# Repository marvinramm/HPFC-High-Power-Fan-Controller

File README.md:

# HPFC – High Power Fan Controller

**Controller for four 12 V server fans with up to 100 W, built into a DIY air filter. It measures the pressure drop across the filter with two BME680 sensors, has its own OLED display and rotary encoder, and joins Zigbee networks, e.g. Home Assistant through Zigbee2MQTT.**

I built the HPFC in 2025 for my own air filter: four Arctic server fans at 8000 RPM move the air through a filter in a closed box. A server fan is loud and needs a lot of power, so it needs a controller that runs it as slowly as possible and tells me when the filter is clogged. The HPFC does that: it compares the air pressure before and after the filter, shows the filter load on the display and on the RGB LED, and reports it to Home Assistant.

## Features

- **4 fan channels** for standard 4-pin PWM fans: 25 kHz PWM, tach input on every channel, 12 V rail switched off completely when the fans stop
- **Up to about 100 W** fan power on one 12 V rail (tested with four Arctic server fans, 8000 RPM)
- **Power supply:**
  - external **12 V** supply on a screw terminal, full fan power
  - or **USB-C Power Delivery**: the CH224K requests 12 V from a PD charger, fan power limited by the firmware
  - LM74700 ideal diode on the USB-C input, so both sources can be connected at the same time without back-feeding the USB port
  - on plain 5 V USB the board runs (display, Zigbee, flashing), the fans stay off
- **Filter monitoring:** two BME680 sensors, one on each side of the filter. The pressure difference is shown as filter load in percent; the LED turns green, yellow or red.
- **Climate data:** temperature and humidity of the air
- **Zigbee 3.0 router** with the ESP32-C6: fan speed 0–100 %, temperature, humidity and filter load as Zigbee endpoints, external converter for [Zigbee2MQTT](firmware/zigbee2mqtt/HPFC.js)
- **Local UI:** 0.96" OLED, rotary encoder with push button, display turns off after 200 s without input
- **ESP32-C6-MINI-1** with native USB on the USB-C port, Tag-Connect TC2050 for programming

## How it works

```mermaid
flowchart LR
    PSU["12 V supply"] --> RAIL["12 V rail"]
    USB["USB-C"] --> PD["CH224K<br/>PD 12 V"]
    USB --> ID["Ideal diode<br/>LM74700 + AO4406"] --> RAIL
    RAIL --> SWITCH["Fan rail switch<br/>AOD403"] --> FANS["4 × server fan"]
    RAIL --> LDO["AMS1117<br/>3.3 V"] --> ESP["ESP32-C6"]
    ESP -- "4 × PWM 25 kHz" --> FANS
    FANS -- "4 × tach" --> ESP
    ESP -- FAN_EN --> SWITCH
    BME1["BME680<br/>before filter"] <-- I²C --> ESP
    BME2["BME680<br/>after filter"] <-- I²C --> ESP
    ESP <-- I²C --> OLED["OLED display"]
    ENC["Rotary encoder"] --> ESP
    ESP --> LED["RGB LED"]
    ESP <-. Zigbee .-> HA["Zigbee2MQTT /<br/>Home Assistant"]
```

## The air filter

The HPFC sits behind the front panel of the filter box. The four fans are mounted under the filter layer and move the air through it. The second BME680 is connected to the I²C header with a short cable and sits on the other side of the filter, so the controller can measure the pressure difference across it.

## Display and status LED

| Page | Content |
|---|---|
| Fan speed | Fan speed in %, power source (`USB 5V`, `USB PD 12V`, `Internal Supply`), Zigbee status |
| Filter pressure | Filter load in % (pressure difference relative to `MAXPADELTA`, default 350 Pa) |

Press the encoder to switch pages. The RGB LED shows the filter load: green below 45 %, yellow from 45 %, red from 70 % – time to change the filter.

## Firmware

HPFOS V0.1.4, Arduino with ESP32 core 3.3. Build instructions, settings, the Zigbee endpoints and the Zigbee2MQTT setup are in [`firmware/README.md`](firmware/README.md).

## Hardware

| | |
|---|---|
| PCB | 2 layers, 71.5 × 50.85 mm, 1.6 mm |
| Schematic | [`hardware/hpfc-v1/HPFC-V1_schematic.pdf`](hardware/hpfc-v1/HPFC-V1_schematic.pdf) |
| BOM | [`hardware/hpfc-v1/HPFC-V1_BOM.csv`](hardware/hpfc-v1/HPFC-V1_BOM.csv), [interactive BOM](hardware/hpfc-v1/HPFC-V1_ibom.html) |
| Design files | EAGLE / Fusion Electronics in [`hardware/hpfc-v1/source`](hardware/hpfc-v1/source) |
| Fabrication data | ODB++ and Gerber in the [release](https://github.com/marvinramm/HPFC-High-Power-Fan-Controller/releases) |

Block description and pin assignment: [`hardware/README.md`](hardware/README.md).

## License

© 2025 Marvin Ramm. Free for **non-commercial** use with attribution:

- Firmware (`firmware/`): [PolyForm Noncommercial 1.0.0](LICENSE)
- Hardware and documentation: [CC BY-NC 4.0](hardware/LICENSE)

Credit "HPFC by Marvin Ramm" with a link to this repository. **Selling boards, kits or products based on the HPFC needs my agreement**, e.g. with a share of the profit – contact marvin@ramm-eng.de. Details are in [LICENSING.md](LICENSING.md).

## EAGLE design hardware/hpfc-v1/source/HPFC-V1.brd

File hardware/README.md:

# Hardware

| File | Content |
|---|---|
| [`hpfc-v1/HPFC-V1_schematic.pdf`](hpfc-v1/HPFC-V1_schematic.pdf) | Schematic (1 sheet, A3) |
| [`hpfc-v1/HPFC-V1_BOM.csv`](hpfc-v1/HPFC-V1_BOM.csv) | Bill of materials, 74 parts |
| [`hpfc-v1/HPFC-V1_ibom.html`](hpfc-v1/HPFC-V1_ibom.html) | Interactive BOM for assembly (download and open in a browser) |
| [`hpfc-v1/source`](hpfc-v1/source) | Schematic and board as EAGLE files (Fusion Electronics 9.7) |

The fabrication data is attached to the [release](https://github.com/marvinramm/HPFC-High-Power-Fan-Controller/releases):

- **ODB++** exported from Fusion Electronics – the original data, accepted directly by most PCB manufacturers
- **Gerber + Excellon drill** generated from the EAGLE board with KiCad's EAGLE importer, including the slotted holes of the USB-C connector. Check them in a Gerber viewer before you order.

## Board

2 layers, 71.5 × 50.85 mm, 1.6 mm, four M3 mounting holes. The display, the encoder, the USB-C port and almost all parts are on the top side. The fan connectors, the 12 V terminal, the bulk capacitor C7 and the I²C header for the second sensor are on the bottom, so the board can sit directly behind a front panel.

| Block | Parts | Function |
|---|---|---|
| USB-C | J7, D1 (SP0503BAHTG) | Power input and native USB, ESD protection |
| USB-PD trigger | IC1 (CH224K) | Requests 12 V from a USB-PD charger |
| Ideal diode | IC3 (LM74700-Q1), Q1 (AO4406AL) | Connects USB-C VBUS to the 12 V rail and blocks reverse current, so an external 12 V supply never feeds back into the USB port |
| External supply | J1 (Phoenix 1711026) | 12 V screw terminal, directly on the 12 V rail |
| Fan rail switch | Q2 (AOD403, P-MOSFET), Q3 (SI2302) | Switches 12 V to all four fans (`FAN_EN`, GPIO22) |
| Fan connectors | J2–J5 (Molex 47053) | Standard 4-pin PWM fan headers: 12 V, GND, PWM (25 kHz), tach |
| Tach filter | R7–R18, C8–C11 | 10 kΩ pull-up to 3.3 V and 2.2 kΩ / 180 pF low-pass for each tach signal |
| 3.3 V | IC4 (AMS1117-3.3) | LDO from the 12 V rail, 1 A |
| MCU | IC5 (ESP32-C6-MINI-1-N4) | Zigbee / Thread, Wi-Fi 6, BLE, 4 MB flash |
| Sensors | IC2 (BME680), JP2 | BME680 on the board, second BME680 on the I²C header JP2 |
| User interface | DSP1 (SSD1306 0.96" OLED), SW1 (PEC12R encoder), LED1 (RGB) | Display, rotary encoder with push button, status LED |
| Programming | J6 (TC2050), SW2 (BOOT), SW3 (RESET) | Tag-Connect with USB D+/D−, EN and BOOT |
| Voltage sense | R2/R5, R3/R6 | Dividers for USB-C VBUS (GPIO1) and the 12 V rail (GPIO2) |

## ESP32-C6 pin assignment

| GPIO | Function | | GPIO | Function |
|---|---|---|---|---|
| 0 | LED blue | | 14–17 | PWM fan 1–4 |
| 1 | USB-C voltage (ADC) | | 18–21 | Tach fan 1–4 |
| 2 | 12 V rail voltage (ADC) | | 22 | `FAN_EN` (12 V fan rail) |
| 3 | LED red | | 23 | LED green |
| 4 | Encoder button | | 12 / 13 | USB D− / D+ |
| 5 / 8 | Encoder A / B | | 9 | BOOT button |
| 6 / 7 | I²C SDA / SCL | | | |

I²C addresses: BME680 on the board `0x77` (address set with JP1), BME680 on JP2 `0x76`, OLED `0x3C`.

## Power budget

The four fans share one 12 V rail. With four Arctic server fans at 8000 RPM the HPFC switches up to about 100 W. Use an external 12 V supply for full speed. On USB-PD the firmware limits the PWM to about 35 %, and on plain 5 V USB the fans stay off (see [firmware](../firmware/README.md#power-source-and-fan-limit)).

## License

The hardware design files and documentation are licensed under [CC BY-NC 4.0](LICENSE). Commercial use needs my agreement, see [LICENSING.md](../LICENSING.md).

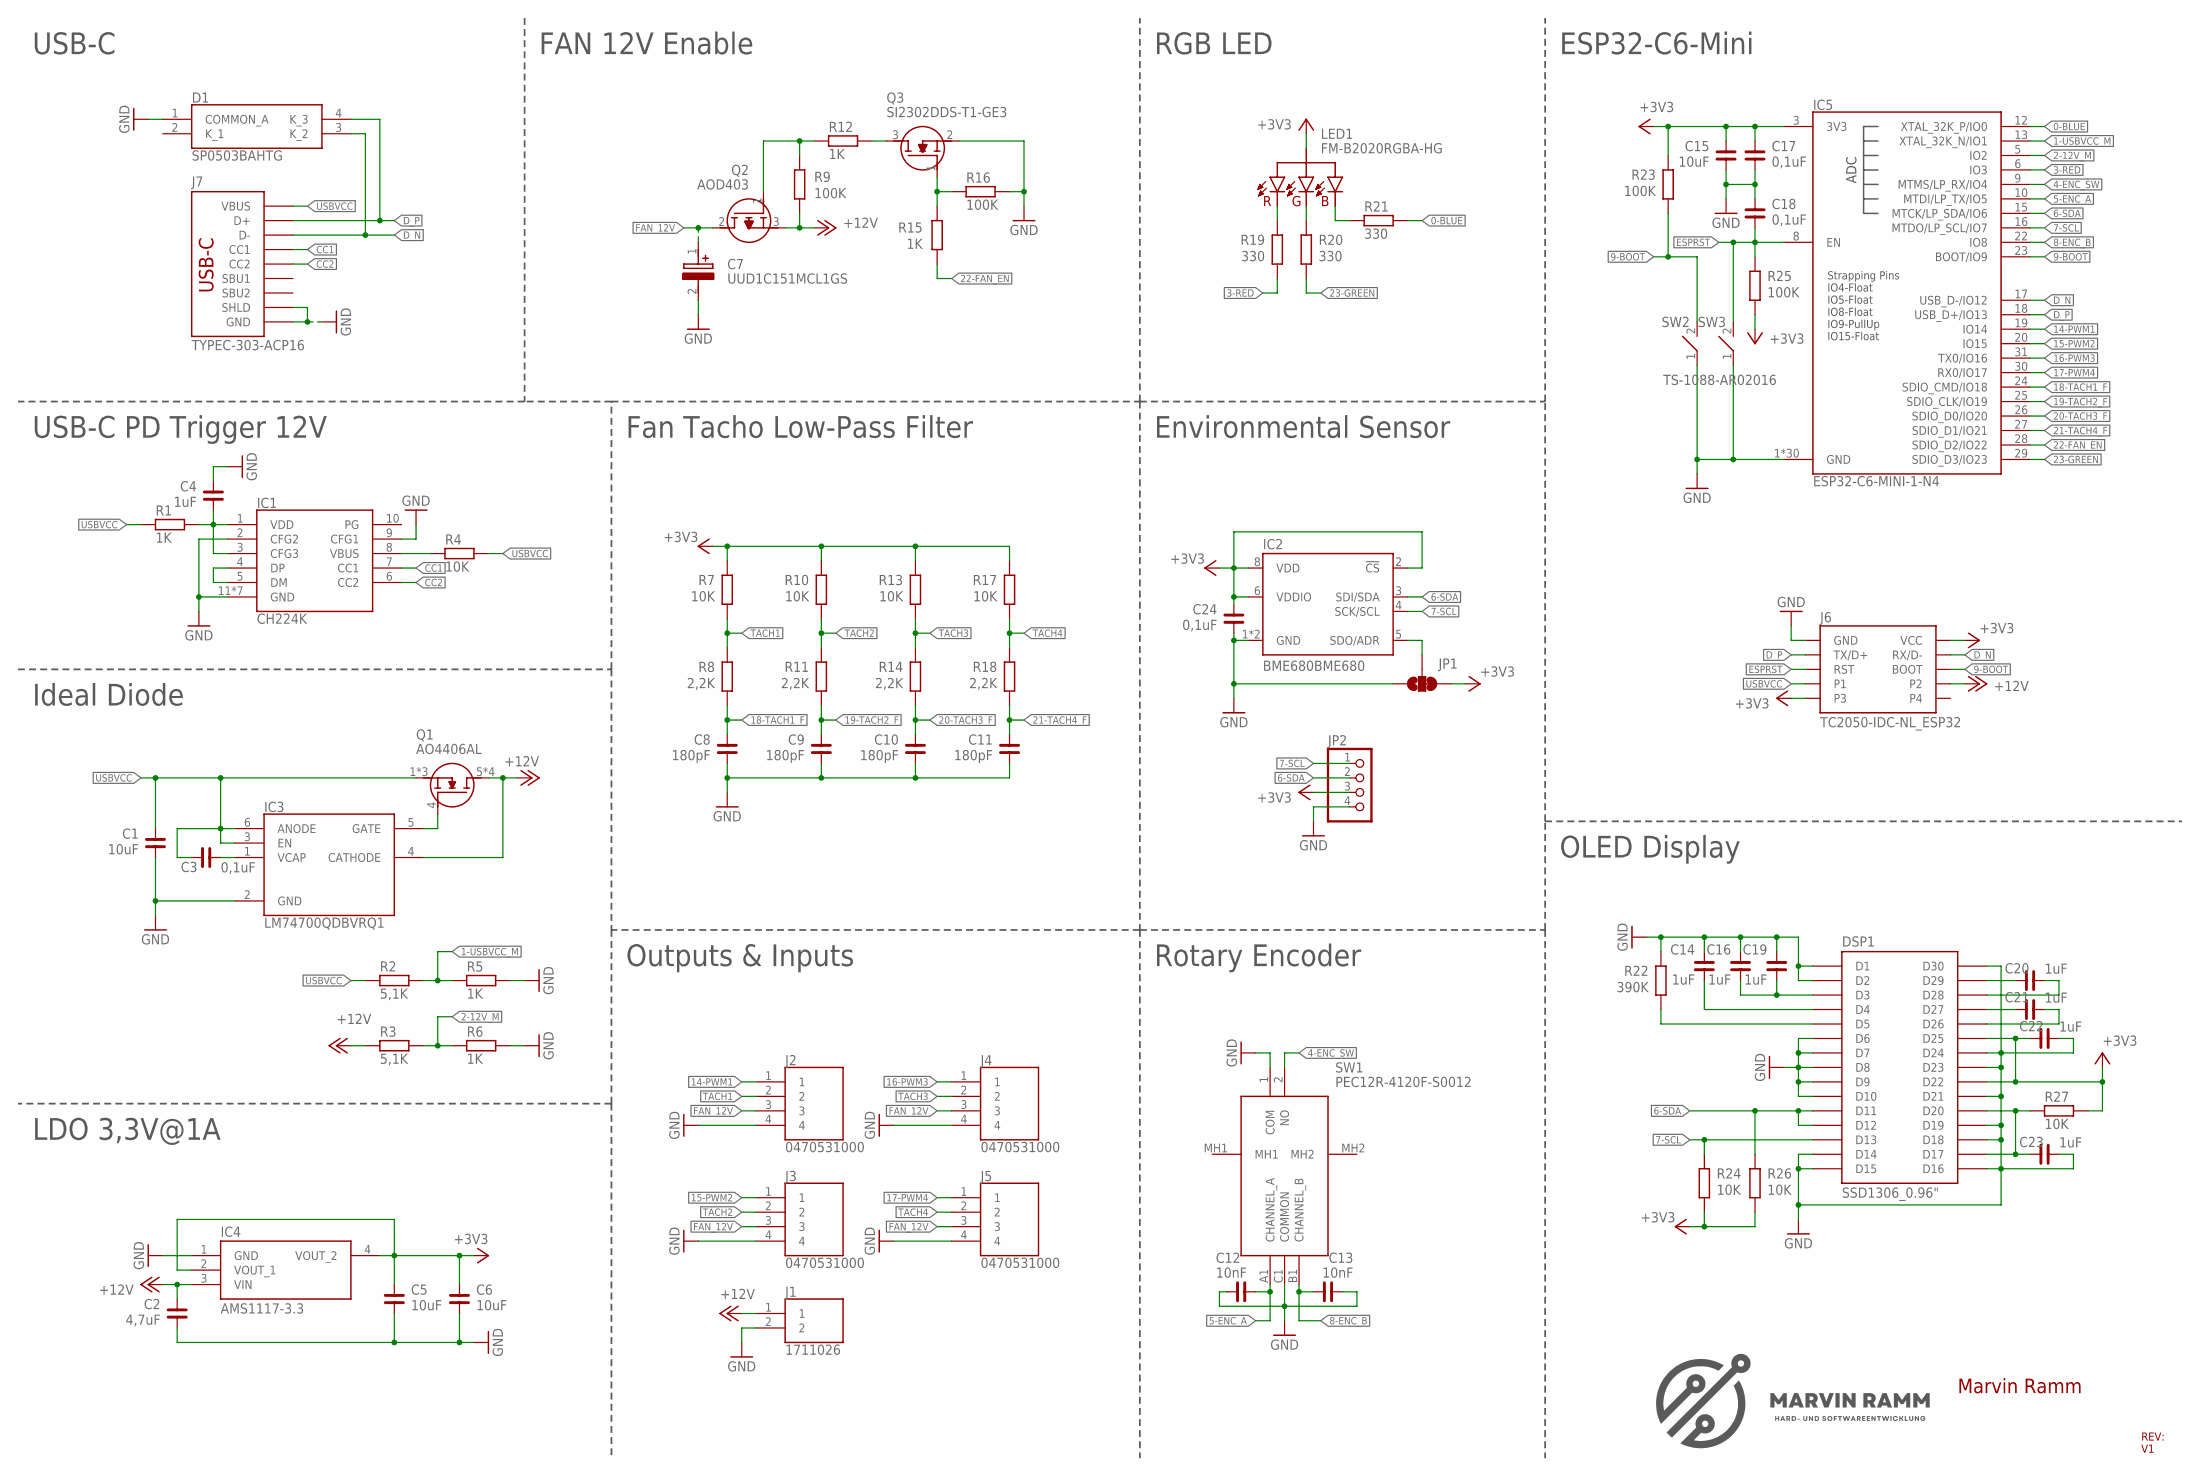
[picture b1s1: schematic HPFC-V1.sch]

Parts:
C1, C5, C6, C15: 10uF; C0603
C2: 4,7uF; C0603
C3, C17, C18, C24: 0,1uF; C0402
C4, C14, C16, C19, C20, C21, C22, C23: 1uF; C0402
C7: UUD1C151MCL1GS; CAPAE660X800N
C8, C9, C10, C11: 180pF; C0402
C12, C13: 10nF; C0402
D1: SP0503BAHTG
DSP1: SSD1306_0.96"
IC1: CH224K; SOP100P600X180-11N
IC2: BME680BME680; LGA3.0X3.0
IC3: LM74700QDBVRQ1; SOT95P280X145-6N
IC4: AMS1117-3.3; SOT229P700X180-4N
IC5: ESP32-C6-MINI-1-N4; ESP32C6MINI1N4
J1: 1711026
J2, J3, J4, J5: 0470531000
J6: TC2050-IDC-NL_ESP32; TC2050-IDC-NL
J7: TYPEC-303-ACP16
JP1: JUMPER-SMT_3_1-NC_TRACE_SILK; SMT-JUMPER_3_1-NC_TRACE_SILK
JP2: PINHD-1X4; 1X04
LED1: FM-B2020RGBA-HG; FMB2020RGBAHG
Q1: AO4406AL; SOIC127P600X175-8N
Q2: AOD403; AOD480
Q3: SI2302DDS-T1-GE3; SOT95P237X112-3N
R1, R5, R6, R12, R15: 1K; R0402
R2, R3: 5,1K; R0402
R4, R7, R10, R13, R17, R24, R26, R27: 10K; R0402
R8, R11, R14, R18: 2,2K; R0402
R9, R16, R23, R25: 100K; R0402
R19, R20, R21: 330; R0402
R22: 390K; R0402
SW1: PEC12R-4120F-S0012; PEC12R4230FS0024
SW2, SW3: TS-1088-AR02016; TS1088AR02016

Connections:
0-BLUE: IC5.12 (XTAL_32K_P/IO0), R21.2
1-USBVCC_M: IC5.13 (XTAL_32K_N/IO1), R2.2, R5.1
2-12V_M: IC5.5 (IO2), R3.2, R6.1
3-RED: IC5.6 (IO3), R19.2
4-ENC_SW: IC5.9 (MTMS/LP_RX/IO4), SW1.2 (NO)
5-ENC_A: C12.2, IC5.10 (MTDI/LP_TX/IO5), SW1.A1 (CHANNEL_A)
6-SDA: DSP1.D11, DSP1.D12, IC2.3 (SDI/SDA), IC5.15 (MTCK/LP_SDA/IO6), JP2.2, R26.1
7-SCL: DSP1.D13, IC2.4 (SCK/SCL), IC5.16 (MTDO/LP_SCL/IO7), JP2.1, R24.1
8-ENC_B: C13.2, IC5.22 (IO8), SW1.B1 (CHANNEL_B)
9-BOOT: IC5.23 (BOOT/IO9), J6.6 (BOOT), R23.2, SW2.2 (NO)
14-PWM1: IC5.19 (IO14), J2.1
15-PWM2: IC5.20 (IO15), J3.1
16-PWM3: IC5.31 (TX0/IO16), J4.1
17-PWM4: IC5.30 (RX0/IO17), J5.1
18-TACH1_F: C8.2, IC5.24 (SDIO_CMD/IO18), R8.2
19-TACH2_F: C9.2, IC5.25 (SDIO_CLK/IO19), R11.2
20-TACH3_F: C10.2, IC5.26 (SDIO_D0/IO20), R14.2
21-TACH4_F: C11.2, IC5.27 (SDIO_D1/IO21), R18.2
22-FAN_EN: IC5.28 (SDIO_D2/IO22), R15.1
23-GREEN: IC5.29 (SDIO_D3/IO23), R20.2
+3V3: C5.2, C6.2, C15.2, C17.2, C22.1, C24.2, DSP1.D22, DSP1.D25, IC2.2 (!CS), IC2.6 (VDDIO), IC2.8 (VDD), IC4.2 (VOUT_1), IC4.4 (VOUT_2), IC5.3 (3V3), J6.2 (VCC), J6.9 (P3), JP1.3, JP2.3, LED1.3 (VCC), R7.1, R10.1, R13.1, R17.1, R23.1, R24.2, R25.2, R26.2, R27.2
+12V: C2.2, IC3.4 (CATHODE), IC4.3 (VIN), J1.1, J6.8 (P2), Q1.5 (D), Q1.6 (D), Q1.7 (D), Q1.8 (D), Q2.3 (S), R3.1, R9.1
CC1: IC1.7 (CC1), J7.A5 (CC1)
CC2: IC1.6 (CC2), J7.B5 (CC2)
D_N: D1.3 (K_2), IC5.17 (USB_D-/IO12), J6.4 (RX/D-), J7.A7 (D-), J7.B7 (D-)
D_P: D1.4 (K_3), IC5.18 (USB_D+/IO13), J6.3 (TX/D+), J7.A6 (D+), J7.B6 (D+)
ESPRST: C18.1, IC5.8 (EN), J6.5 (RST), R25.1, SW3.2 (NO)
FAN_12V: C7.1 (+), J2.3, J3.3, J4.3, J5.3, Q2.2 (D)
GND: C1.1, C2.1, C4.2, C5.1, C6.1, C7.2 (-), C8.1, C9.1, C10.1, C11.1, C12.1, C13.1, C14.2, C15.1, C16.2, C17.1, C18.2, C19.2, C22.2, C23.2, C24.1, D1.1 (COMMON_A), DSP1.D1, DSP1.D2, DSP1.D6, DSP1.D7, DSP1.D8, DSP1.D9, DSP1.D10, DSP1.D14, DSP1.D15, DSP1.D16, DSP1.D18, DSP1.D19, DSP1.D21, DSP1.D23, DSP1.D24, DSP1.D30, IC1.2 (CFG2), IC1.9 (CFG1), IC1.11 (GND), IC1.P$1 (GND), IC1.P$2 (GND), IC1.P$3 (GND), IC1.P$4 (GND), IC1.P$5 (GND), IC1.P$6 (GND), IC2.1 (GND), IC2.7 (GND), IC3.2 (GND), IC4.1 (GND), IC5.1 (GND), IC5.2 (GND), IC5.11 (GND), IC5.14 (GND), IC5.36 (GND), IC5.37 (GND), IC5.38 (GND), IC5.39 (GND), IC5.40 (GND), IC5.41 (GND), IC5.42 (GND), IC5.43 (GND), IC5.44 (GND), IC5.45 (GND), IC5.46 (GND), IC5.47 (GND), IC5.48 (GND), IC5.49 (GND), IC5.50 (GND), IC5.51 (GND), IC5.52 (GND), IC5.53 (GND), IC5.54 (GND), IC5.55 (GND), IC5.56 (GND), IC5.57 (GND), IC5.58 (GND), IC5.59 (GND), IC5.60 (GND), IC5.61 (GND), J1.2, J2.4, J3.4, J4.4, J5.4, J6.1 (GND), J7.A1 (GND), J7.A12 (GND), J7.B1 (GND), J7.B12 (GND), J7.PD1 (SHLD), J7.PD2 (SHLD), J7.PD3 (SHLD), J7.PD4 (SHLD), JP1.1, JP2.4, Q3.2 (S), R5.2, R6.2, R16.2, R22.1, SW1.1 (COM), SW1.C1 (COMMON), SW2.1 (COM), SW3.1 (COM)
unnamed: C4.1, IC1.1 (VDD), IC1.3 (CFG3), R1.2
unnamed: IC1.4 (DP), IC1.5 (DM)
unnamed: IC1.8 (VBUS), R4.1
unnamed: IC3.5 (GATE), Q1.4 (G1)
unnamed: LED1.2 (B), R21.1
unnamed: IC2.5 (SDO/ADR), JP1.2
unnamed: C3.2, IC3.1 (VCAP)
unnamed: Q2.1 (G), R9.2, R12.1
unnamed: Q3.3 (D), R12.2
unnamed: Q3.1 (G), R15.2, R16.1
unnamed: LED1.1 (R), R19.1
unnamed: LED1.4 (G), R20.1
unnamed: DSP1.D5, R22.2
unnamed: C16.1, C19.1, DSP1.D3
unnamed: C20.1, DSP1.D29
unnamed: C14.1, DSP1.D4
unnamed: C20.2, DSP1.D28
unnamed: C21.1, DSP1.D27
unnamed: C21.2, DSP1.D26
unnamed: C23.1, DSP1.D17, DSP1.D20, R27.1
TACH1: J2.2, R7.2, R8.1
TACH2: J3.2, R10.2, R11.1
TACH3: J4.2, R13.2, R14.1
TACH4: J5.2, R17.2, R18.1
USBVCC: C1.2, C3.1, IC3.3 (EN), IC3.6 (ANODE), J6.7 (P1), J7.A4 (VBUS), J7.A9 (VBUS), J7.B4 (VBUS), J7.B9 (VBUS), Q1.1 (S), Q1.2 (S), Q1.3 (S), R1.1, R2.1, R4.2

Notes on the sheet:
REV: V1
Marvin Ramm
USB-C
USB-C PD Trigger 12V
Ideal Diode
LDO 3,3V@1A
Outputs & Inputs
Fan Tacho Low-Pass Filter
FAN 12V Enable
RGB LED
ESP32-C6-Mini
Environmental Sensor
Rotary Encoder
OLED Display

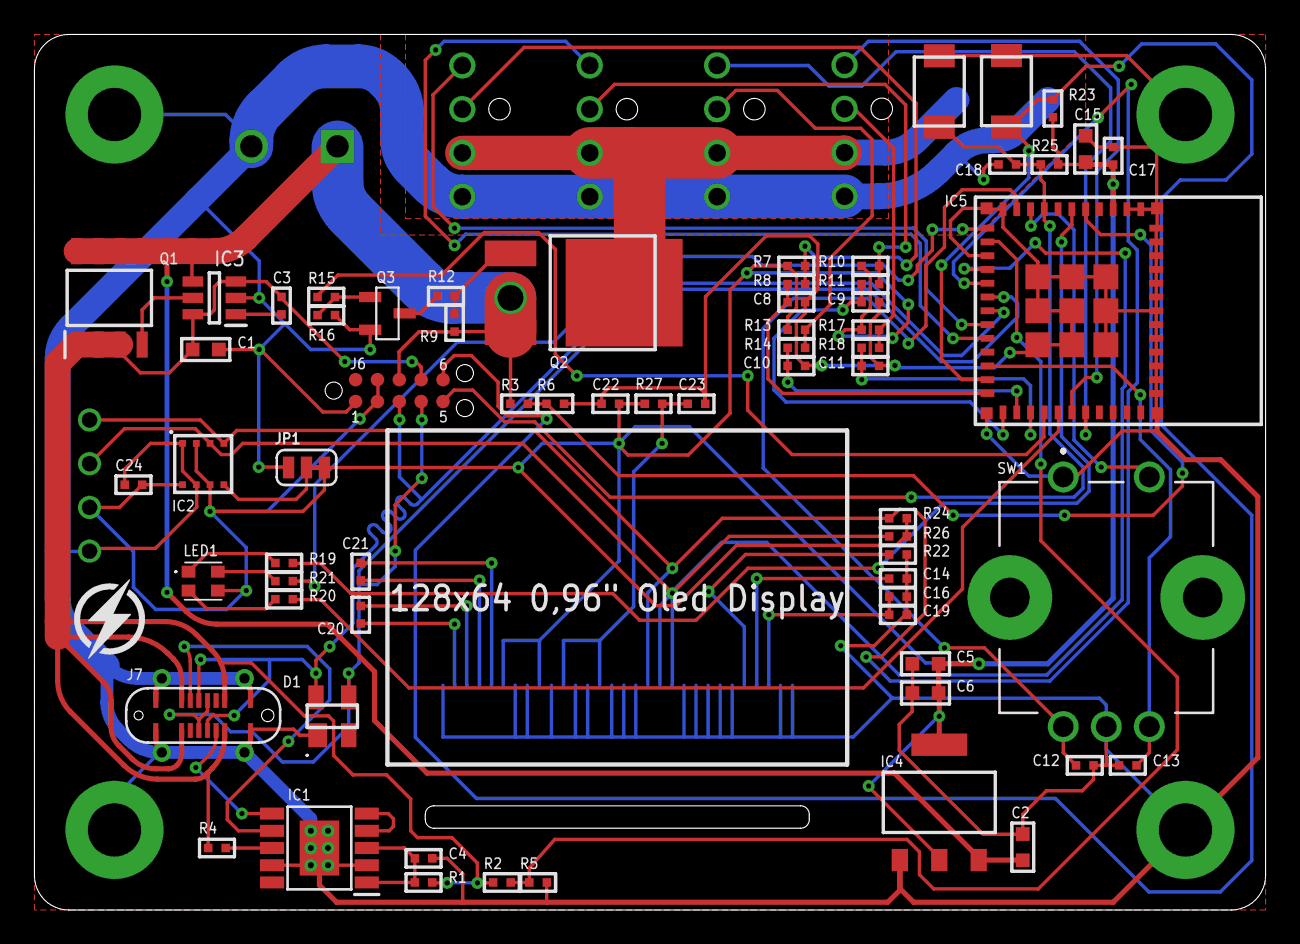
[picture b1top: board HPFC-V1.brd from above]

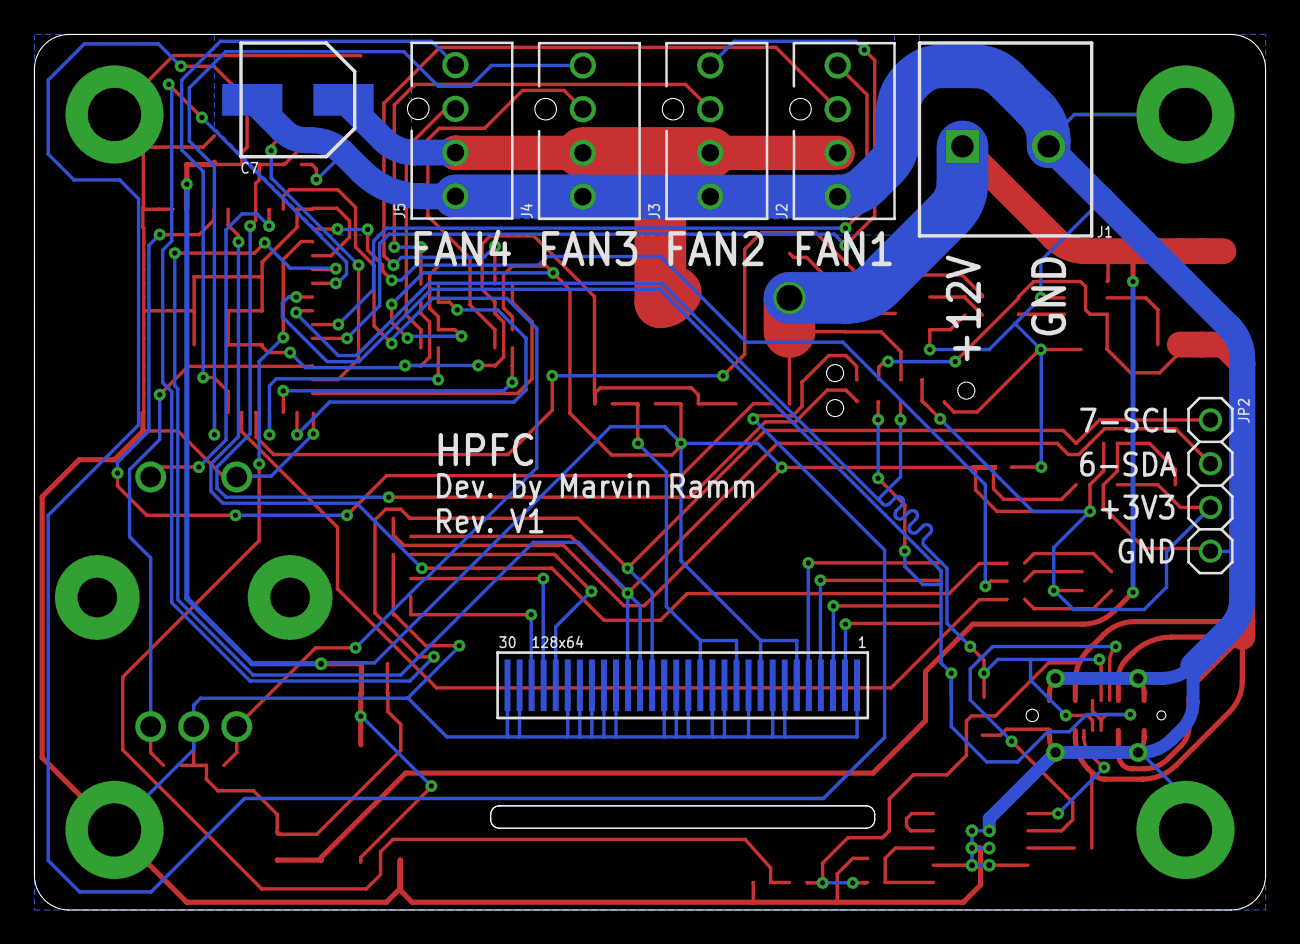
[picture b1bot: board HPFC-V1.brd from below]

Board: 2 copper layers, 71.5 x 50.9 mm, 74 parts (8 on the bottom side), 54 nets.

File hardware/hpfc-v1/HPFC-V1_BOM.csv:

Reference,Qty,Value / Part,Package,Description
"C1, C5, C6, C15",4,10 µF,0603,Ceramic capacitor
C2,1,4.7 µF,0603,Ceramic capacitor
"C3, C17, C18, C24",4,100 nF,0402,Ceramic capacitor
"C4, C14, C16, C19, C20, C21, C22, C23",8,1 µF,0402,Ceramic capacitor
C7,1,150 µF 16 V (UUD1C151MCL1GS),SMD 6.6 x 8 mm,"Aluminium electrolytic, 12 V fan rail bulk capacitor"
"C8, C9, C10, C11",4,180 pF,0402,Tach low-pass filter
"C12, C13",2,10 nF,0402,Encoder debounce
D1,1,SP0503BAHTG,SOT-143,ESD protection USB-C
DSP1,1,"SSD1306 0.96"" OLED 128x64",FPC 30-pin,Display (I2C 0x3C)
IC1,1,CH224K,ESSOP-10,"USB-PD sink controller, requests 12 V"
IC2,1,BME680,LGA 3x3,Pressure / temperature / humidity / gas sensor (on board)
IC3,1,LM74700QDBVRQ1,SOT-23-6,Ideal-diode controller for the USB-C input
IC4,1,AMS1117-3.3,SOT-223,"3.3 V LDO, 1 A"
IC5,1,ESP32-C6-MINI-1-N4,Module,MCU with Zigbee / Thread / Wi-Fi 6 / BLE
J1,1,Phoenix Contact 1711026,2-pin terminal block 5.08 mm,External 12 V input
"J2, J3, J4, J5",4,Molex 0470531000,4-pin 2.54 mm,4-pin PWM fan connectors
J6,1,TC2050-IDC-NL,Tag-Connect,Programming / serial
J7,1,TYPEC-303-ACP16,USB-C 16-pin,USB-C power (PD) and USB
JP1,1,Solder jumper 3-pad,SMD,BME680 I2C address select
JP2,1,Pin header 1x04,2.54 mm,I2C header for the second BME680
LED1,1,FM-B2020RGBA-HG,2020,RGB status LED
Q1,1,AO4406AL,SO-8,N-MOSFET for the ideal diode
Q2,1,AOD403,DPAK,"P-MOSFET, 12 V fan rail switch"
Q3,1,SI2302DDS-T1-GE3,SOT-23,"N-MOSFET, gate driver for Q2"
"R1, R5, R6, R12, R15",5,1 kΩ,0402,Resistor
"R2, R3",2,5.1 kΩ,0402,Resistor (voltage dividers)
"R4, R7, R10, R13, R17, R24, R26, R27",8,10 kΩ,0402,Resistor
"R8, R11, R14, R18",4,2.2 kΩ,0402,Resistor (tach filter)
"R9, R16, R23, R25",4,100 kΩ,0402,Resistor
"R19, R20, R21",3,330 Ω,0402,Resistor (LED)
R22,1,390 kΩ,0402,Resistor (OLED IREF)
SW1,1,Bourns PEC12R-4120F-S0012,THT,Rotary encoder with push button
"SW2, SW3",2,TS-1088-AR02016,SMD,Tactile switch (reset / boot)

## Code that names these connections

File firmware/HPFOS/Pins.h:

// HPFOS - firmware for the HPFC High Power Fan Controller
// Copyright (c) 2025 Marvin Ramm - PolyForm Noncommercial 1.0.0, see LICENSING.md

#ifndef PINS_H
#define PINS_H

#define SDA 6
#define SCL 7

#define FAN_EN 22

#define LED_BLUE 0
#define LED_RED  3
#define LED_GREEN 23

#define BOOT 9

#define TACH1 18
#define TACH2 19
#define TACH3 20
#define TACH4 21

#define FAN1 14
#define FAN2 15
#define FAN3 16
#define FAN4 17

#define ENC_A 5
#define ENC_B 8
#define ENC_SW 4

#define USBVCC_M 1
#define VCC_M    2

#define BME_IN_ADRESS 0x77
#define BME_OUT_ADRESS 0x76
#define DISPLAY_ADRESS 0x3C

#endif

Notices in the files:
README.md:
License: PolyForm Noncommercial
License: CC BY-NC 4.0
parts and their libraries:
rc-master-smd: Copyright (C) 2007, Bob Starr
SparkFun-Jumpers: Licensing: Creative Commons ShareAlike 4.0 International - https://creativecommons.org/licenses/by-sa/4.0
